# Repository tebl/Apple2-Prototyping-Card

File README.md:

# Apple ][ Prototyping Card

**CURRENTLY UNTESTED!**

After a recent purchase of an old Apple //e I concluded that most expansions I wanted were, as most things Apple these days, excessively priced - so I took it upon myself to make them myself instead. Bold statements aside, this was something that used to be an option back in the old days when Steve Wozniak was still central to the engineering genius that went into these machines.

First step on that route was obtaining something I could plug into one of the slots, so with a slightly altered edge connector footprint obtained from [Xander's 8-bit fun](https://xjmaas.wordpress.com/my-apple-collection/apple-edge-connector-template-for-eagle/) the rest was hours of putting in holes for the prototyping areas. I wanted as much as possible out of the available space, but still be able to close the lid on all the mess I'm going to make so the original card dimensions as specified in [Apple IIgs Tech Note #28](http://www.1000bit.it/support/manuali/apple/technotes/iigs/tn.iigs.028.html) was followed within my ability to work with inches (thanks for that you imperial something or others).

The edge connector has 50 pins, a description of what function each of them serves can be found [online](http://osites.tripod.com/peripheral.html) - not that not all of them are present on every machine and type of slot available. All of the signals and power rails are available from a breakout connector above the edge connector, all of the pin names have been added to the reverse side for easier soldering.

Several versions of the prototyping boards are available, with size and cost being the main difference between them at this point in time. The compact (smaller) card should fit within the cheapest option for most Chinese PCB fabrication services, and so would be the perfect place to start when experimenting with the easier stuff. The fullsize version should give all the space you need for most projects. See PCB layout previews below to get an impression of how these will look.

## Versions available
The following versions are currently available, I use PCBway and the compact/small one should be around 5$ for 10 of them. Click the cards to go to the relevant details for the card, the order URLs point to my shared projects on PCBway:
- [Compact prototyping card](https://github.com/tebl/Apple2-Prototyping-Card/tree/master/small)
- [Fullsize prototyping card](https://github.com/tebl/Apple2-Prototyping-Card/tree/master/fullsize)

If you would like to have a copy of one or more modules, what you'll need to do is zip up the contents of the export directory for each module and give that to your favourite PCB fabrication plant. Personally I prefer to use [PCBWay](https://www.pcbway.com/setinvite.aspx?inviteid=88707), the small one fits within the 5$ price and new accounts even get the first one free! Please use the supplied link when signing up to help me support this project, I'll get a small discount on future orders and hopefully I can afford to keep developing new and exciting stuff for old machines.

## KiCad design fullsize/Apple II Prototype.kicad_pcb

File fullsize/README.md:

# Apple ][ Fullsize Prototyping Card

Several versions of the prototyping boards are available that can be used with the Apple ][, //e and //gs, with size and cost being the main difference between them at this point in time. The smaller one should fit within the cheapest option for most Chinese PCB fabrication services, and so would be the perfect place to start when experimenting with the easier stuff. The fullsize version should give all the space you need for most projects. For more general information, see the [main project page](https://github.com/tebl/Apple2-Prototyping-Card).

# Schematic
The supplied KiCad files should be sufficient as both a schematic and as a starting
point for ordering PCBs, the schematic is also available in
[PDF-format](https://github.com/tebl/Apple2-Prototyping-Card/raw/master/fullsize/export/Apple%20II%20Prototype.pdf). You can refer to the BOM below for a list of suggested components to use, part numbers in parenthesis are optional and is not required.

# BOM
Given that this is a prototyping card, it's completely up to you to decide what actually goes on the card - permanently, or temporarily when you've found the need to refine your current designs. The BOM therefore consists only of the PCB itself, but I've kept this section in keeping with the structure used with my other various projects.

| Reference | Item                                  | Count  |
| --------- | ------------------------------------- | ------ |
| PCB       | Fabricate yourself using KiCad files  |     1  |

If you would like to have a copy of one or more modules, what you'll need to do is zip up the contents of the export directory for each module and give that to your favourite PCB fabrication plant. Personally I prefer to use [PCBWay](https://www.pcbway.com/setinvite.aspx?inviteid=88707), each module has been designed to fit inside the 5$ dimensions. Use the link provided when signing up to support this project!

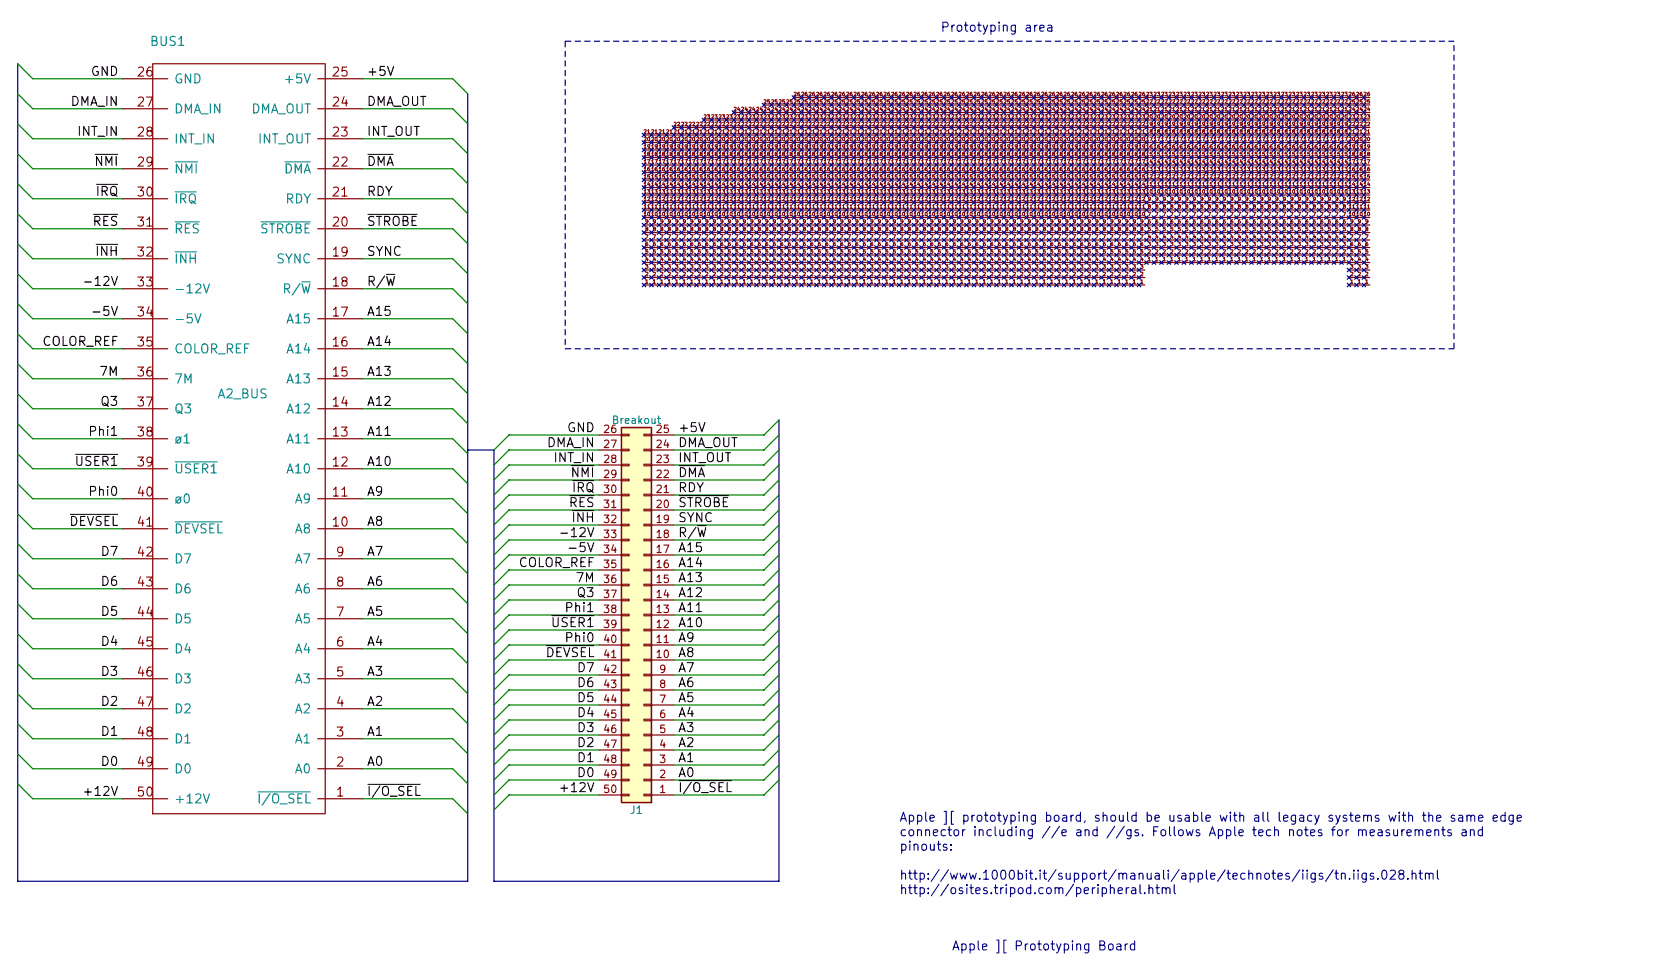
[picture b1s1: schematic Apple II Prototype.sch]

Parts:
BUS1: A2_BUS; BUS_A2
J1: Breakout
P1, P2, P3, P4, P5, P6, P7, P8, P36, P37, P38, P39, P40, P41, P42, P43, P44, P45, P46, P47, P48, P49, P50, P51, P52, P53, P54, P55, P56, P57, P58, P59, P60, P66, P67, P68, P69, P70, P71, P72, P73, P74, P75, P76, P77, P78, P79, P80, P81, P82: Prototype_26; prototype_26
P9, P10, P11, P12, P13, P14, P15, P16, P17, P18, P19, P20, P21, P22, P23, P24, P25, P26, P27, P28, P29, P30, P31, P32, P33, P34, P35, P86, P87, P88, P89: Prototype_23; prototype_23
P61, P62, P83, P85: Prototype_24; prototype_24
P63, P64, P65, P84: Prototype_25; prototype_25
P90, P91, P92, P93: Prototype_22; prototype_22
P94, P95, P96, P97: Prototype_21; prototype_21

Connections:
/7M: BUS1.36 (7M), J1.36
/+5V: BUS1.25 (+5V), J1.25
/+12V: BUS1.50 (+12V), J1.50
/-5V: BUS1.34 (-5V), J1.34
/-12V: BUS1.33 (-12V), J1.33
/A0: BUS1.2 (A0), J1.2
/A1: BUS1.3 (A1), J1.3
/A2: BUS1.4 (A2), J1.4
/A3: BUS1.5 (A3), J1.5
/A4: BUS1.6 (A4), J1.6
/A5: BUS1.7 (A5), J1.7
/A6: BUS1.8 (A6), J1.8
/A7: BUS1.9 (A7), J1.9
/A8: BUS1.10 (A8), J1.10
/A9: BUS1.11 (A9), J1.11
/A10: BUS1.12 (A10), J1.12
/A11: BUS1.13 (A11), J1.13
/A12: BUS1.14 (A12), J1.14
/A13: BUS1.15 (A13), J1.15
/A14: BUS1.16 (A14), J1.16
/A15: BUS1.17 (A15), J1.17
/COLOR_REF: BUS1.35 (COLOR_REF), J1.35
/D0: BUS1.49 (D0), J1.49
/D1: BUS1.48 (D1), J1.48
/D2: BUS1.47 (D2), J1.47
/D3: BUS1.46 (D3), J1.46
/D4: BUS1.45 (D4), J1.45
/D5: BUS1.44 (D5), J1.44
/D6: BUS1.43 (D6), J1.43
/D7: BUS1.42 (D7), J1.42
/DMA_IN: BUS1.27 (DMA_IN), J1.27
/DMA_OUT: BUS1.24 (DMA_OUT), J1.24
/GND: BUS1.26 (GND), J1.26
/INT_IN: BUS1.28 (INT_IN), J1.28
/INT_OUT: BUS1.23 (INT_OUT), J1.23
/Phi0: BUS1.40 (ø0), J1.40
/Phi1: BUS1.38 (ø1), J1.38
/Q3: BUS1.37 (Q3), J1.37
/R/~W: BUS1.18 (R/~W), J1.18
/RDY: BUS1.21 (RDY), J1.21
/SYNC: BUS1.19 (SYNC), J1.19
/~DEVSEL: BUS1.41 (~DEVSEL), J1.41
/~DMA: BUS1.22 (~DMA), J1.22
/~I/O_SEL: BUS1.1 (~I/O_SEL), J1.1
/~INH: BUS1.32 (~INH), J1.32
/~IRQ: BUS1.30 (~IRQ), J1.30
/~NMI: BUS1.29 (~NMI), J1.29
/~RES: BUS1.31 (~RES), J1.31
/~STROBE: BUS1.20 (~STROBE), J1.20
/~USER1: BUS1.39 (~USER1), J1.39

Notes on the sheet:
Apple ][ Prototyping Board
Apple ][ prototyping board, should be usable with all legacy systems with the same edge connector including //e and //gs. Follows Apple tech notes for measurements and pinouts: http://www.1000bit.it/support/manuali/apple/technotes/iigs/tn.iigs.028.html http://osites.tripod.com/peripheral.html
Prototyping area

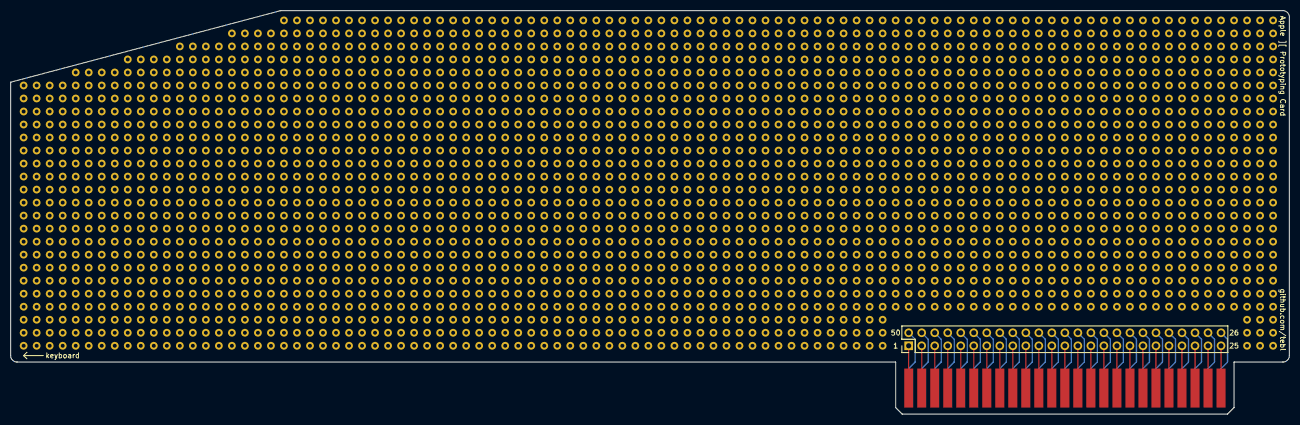
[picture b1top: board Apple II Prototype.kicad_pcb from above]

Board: 2 copper layers, 249.6 x 78.7 mm, 99 parts (0 on the bottom side), 50 nets.

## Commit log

2019-08-20 Blank layout
2019-08-20 First layout draft
2019-08-21 Removed silkscreen from bus footprint
2019-08-21 Added source notices to schematic
2019-08-21 Reorganized files
2019-08-21 Fixed ERC errors
2019-08-21 Added fullsize board and signal names to boards
2019-08-21 Gerber export
2019-08-21 Added README draft
2019-08-23 Added README for each version
